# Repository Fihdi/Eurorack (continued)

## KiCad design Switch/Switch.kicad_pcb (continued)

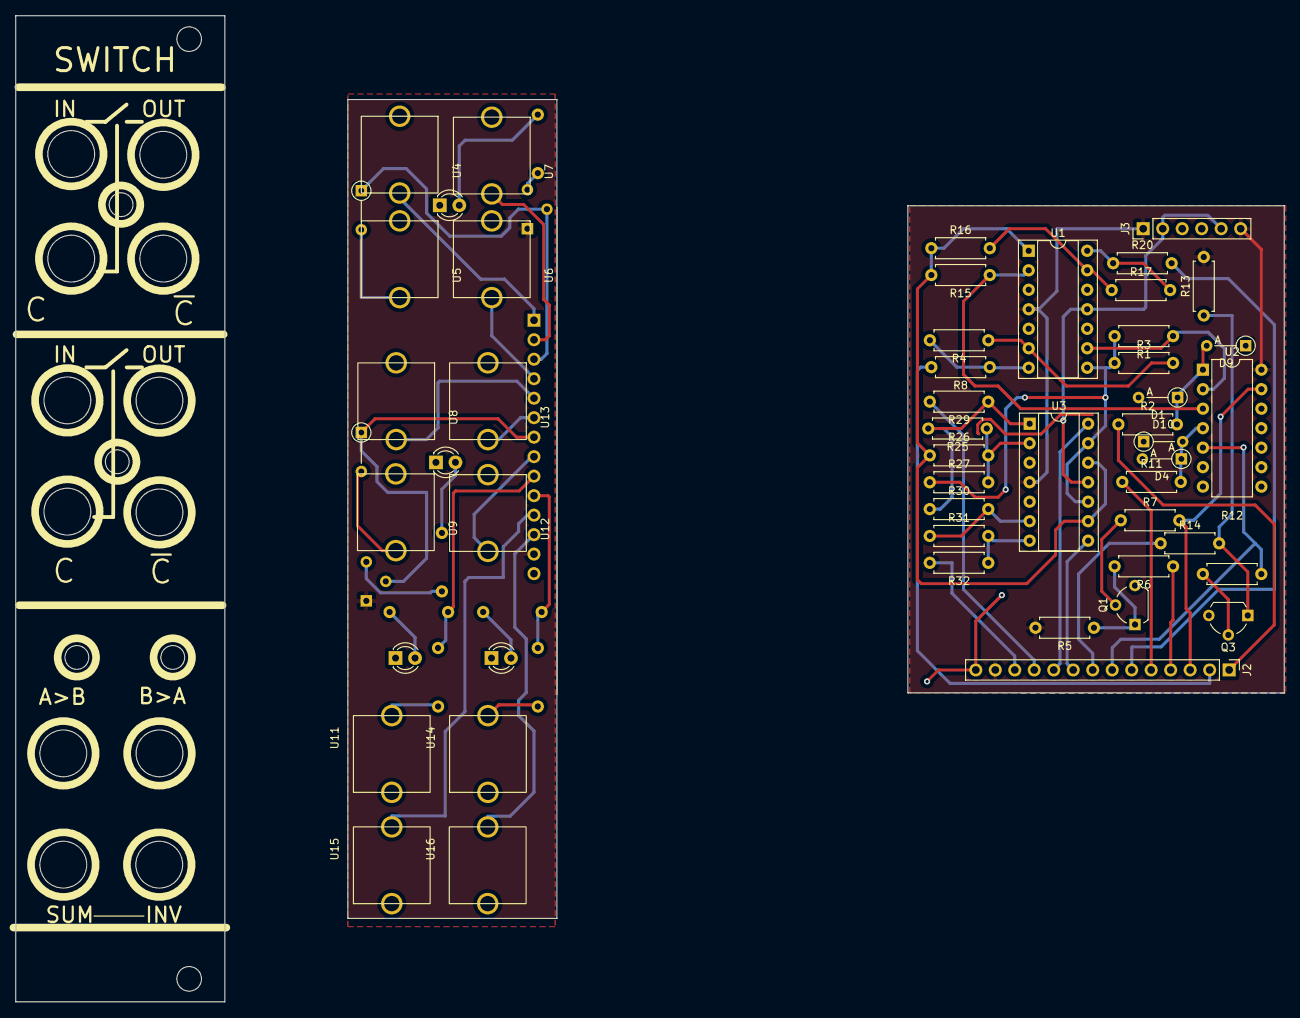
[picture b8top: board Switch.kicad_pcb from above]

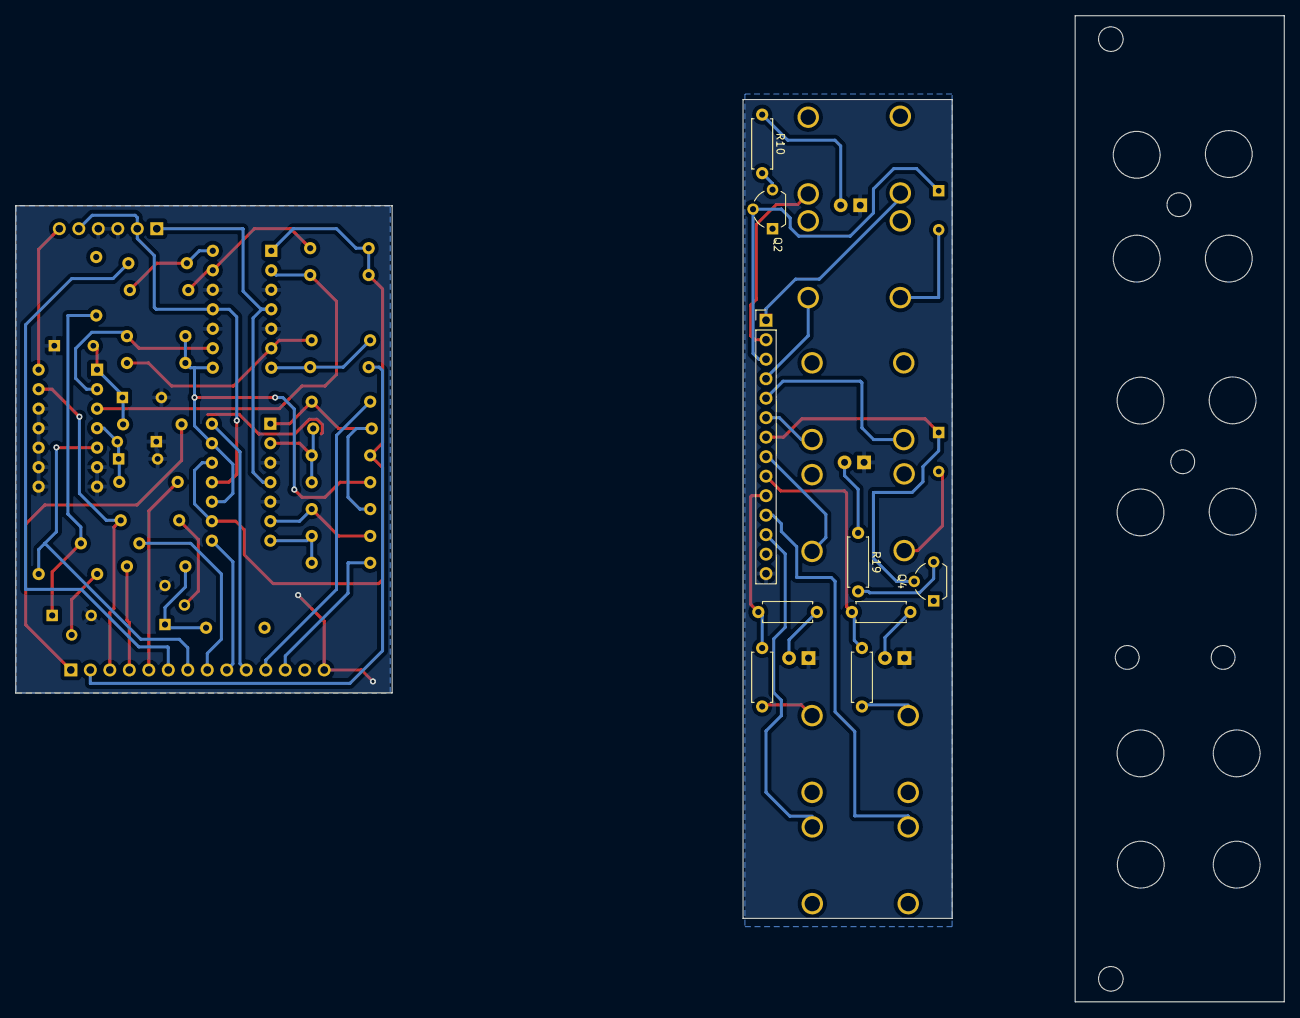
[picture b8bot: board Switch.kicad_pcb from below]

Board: 2 copper layers, 165.3 x 128.5 mm, 61 parts (9 on the bottom side), 43 nets.
